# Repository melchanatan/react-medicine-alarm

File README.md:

# medicine alarm
this is a React website for setting alarm clock connected to ESP32

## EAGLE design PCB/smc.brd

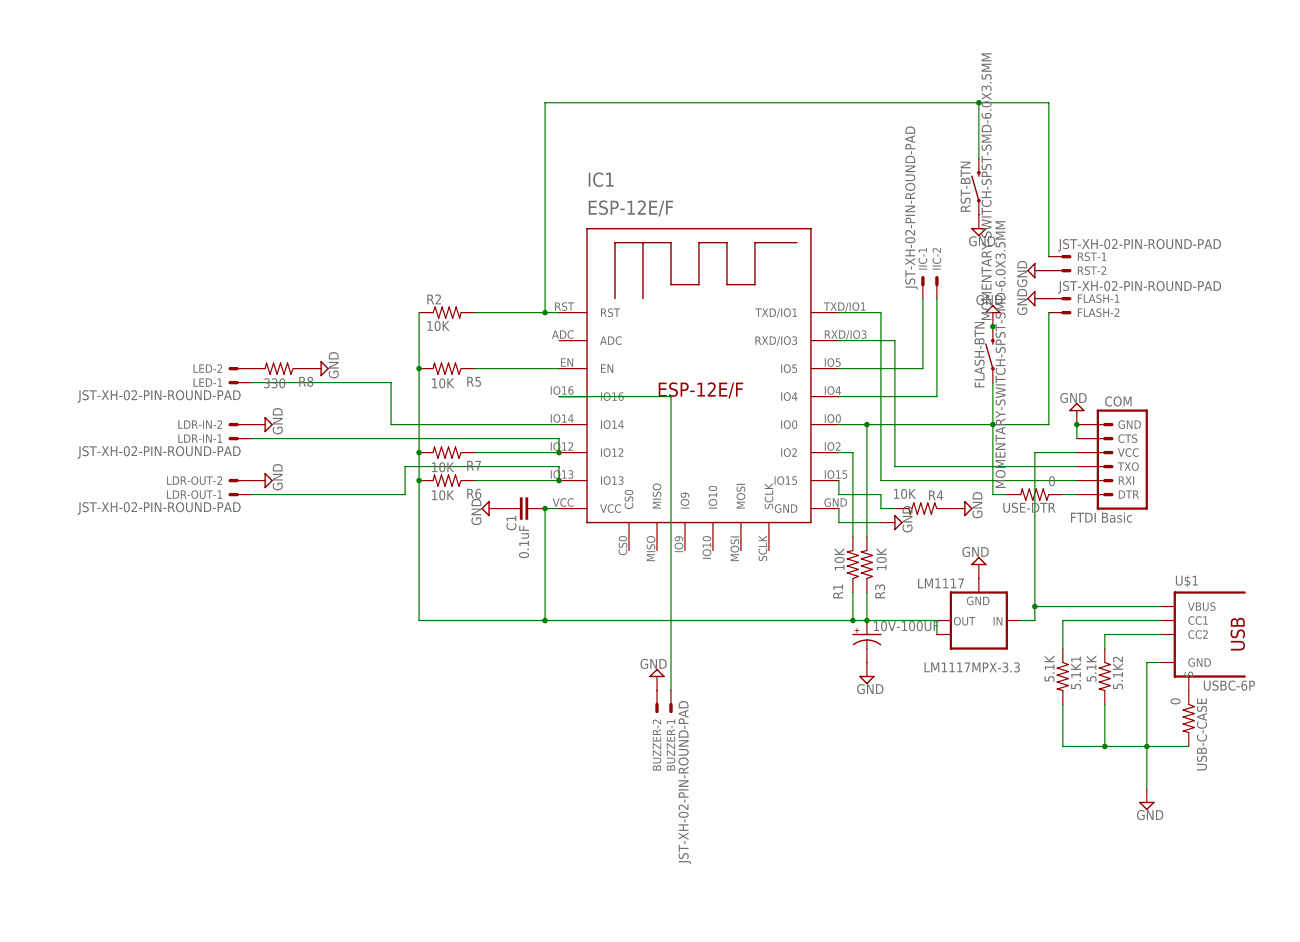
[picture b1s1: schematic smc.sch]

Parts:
5.1K1, 5.1K2: 5.1K; 0603-RES
10V-100UF: CPOL-USA/3216-18W; A/3216-18W
BUZZER: JST-XH-02-PIN-ROUND-PAD; JST-XH-02-PACKAGE-ROUND-PAD
C1: 0.1uF; 0603-CAP
COM: FTDI Basic; 1X06
FLASH: JST-XH-02-PIN-ROUND-PAD; JST-XH-02-PACKAGE-ROUND-PAD
FLASH-BTN: MOMENTARY-SWITCH-SPST-SMD-6.0X3.5MM; TACTILE_SWITCH_SMD_6.0X3.5MM
IC1: ESP-12E/F; ESP-12E
IIC: JST-XH-02-PIN-ROUND-PAD; JST-XH-02-PACKAGE-ROUND-PAD
LDR-IN: JST-XH-02-PIN-ROUND-PAD; JST-XH-02-PACKAGE-ROUND-PAD
LDR-OUT: JST-XH-02-PIN-ROUND-PAD; JST-XH-02-PACKAGE-ROUND-PAD
LED: JST-XH-02-PIN-ROUND-PAD; JST-XH-02-PACKAGE-ROUND-PAD
LM1117: LM1117MPX-3.3; SOT223
R1, R2, R3, R4, R5, R6, R7: 10K; 0603-RES
R8: 330; 0603-RES
RST: JST-XH-02-PIN-ROUND-PAD; JST-XH-02-PACKAGE-ROUND-PAD
RST-BTN: MOMENTARY-SWITCH-SPST-SMD-6.0X3.5MM; TACTILE_SWITCH_SMD_6.0X3.5MM
U$1: USBC-6P; USCX-06FX-XXMX-01
USB-C-CASE: 0; 0603-RES
USE-DTR: 0; 0603-RES

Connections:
3V3: 10V-100UF.+, C1.1, IC1.VCC, LM1117.2 (OUT), LM1117.TAB (OUT1), R1.1, R2.1, R3.1, R5.2, R6.2, R7.2
5V: COM.4 (VCC), LM1117.3 (IN), U$1.VBUS1 (VBUS), U$1.VBUS2 (VBUS)
GND: 5.1K1.2, 5.1K2.2, 10V-100UF.-, BUZZER.2, C1.2, COM.5 (CTS), COM.6 (GND), FLASH.1, FLASH-BTN.2, IC1.GND, LDR-IN.2, LDR-OUT.2, LM1117.1 (GND), R4.1, R8.1, RST.2, RST-BTN.1, U$1.GND1 (GND), U$1.GND2 (GND), USB-C-CASE.2
IO0: FLASH.2, FLASH-BTN.1, IC1.IO0, R3.2, USE-DTR.2
IO2: IC1.IO2, R1.2
unnamed: IC1.IO15, R4.2
unnamed: IC1.EN, R5.1
unnamed: IC1.IO12, LDR-IN.1, R7.1
unnamed: IC1.IO13, LDR-OUT.1, R6.1
unnamed: LED.2, R8.2
unnamed: COM.3 (TXO), IC1.RXD/IO3
unnamed: COM.2 (RXI), IC1.TXD/IO1
unnamed: COM.1 (DTR), USE-DTR.1
unnamed: U$1.SHIELD1 (S), U$1.SHIELD2 (S), U$1.SHIELD3 (S), U$1.SHIELD4 (S), USB-C-CASE.1
unnamed: IC1.IO14, LED.1
unnamed: 5.1K2.1, U$1.CC2
unnamed: 5.1K1.1, U$1.CC1
unnamed: BUZZER.1, IC1.IO16
unnamed: IC1.IO5, IIC.1
unnamed: IC1.IO4, IIC.2
RST: IC1.RST, R2.2, RST.1, RST-BTN.2

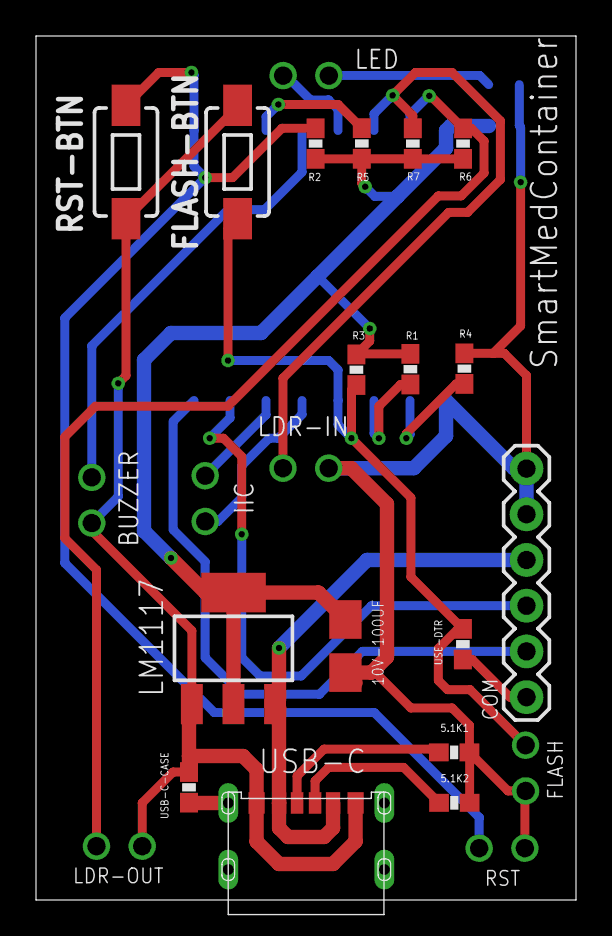
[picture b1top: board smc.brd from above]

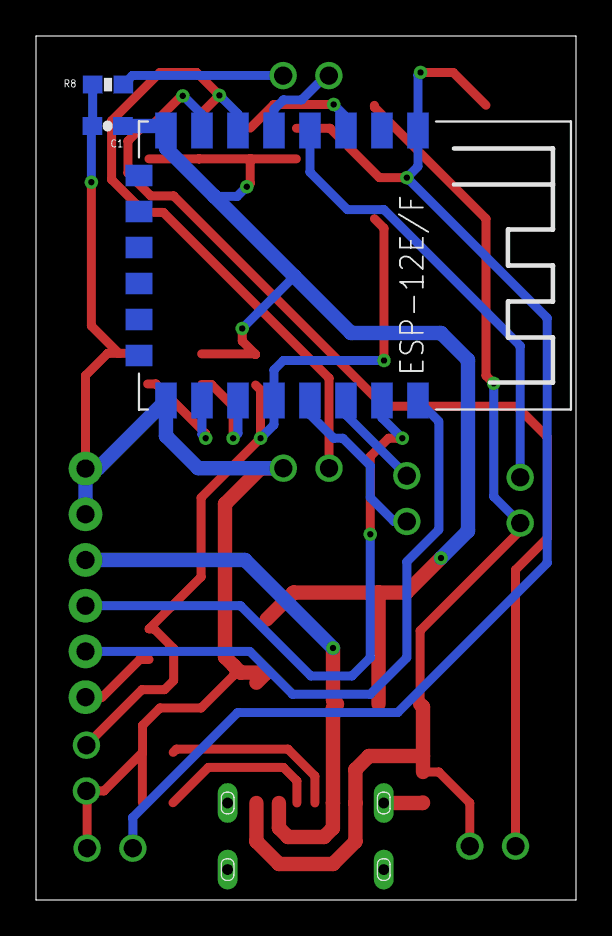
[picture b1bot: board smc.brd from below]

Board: 2 copper layers, 30.0 x 48.0 mm, 27 parts (3 on the bottom side), 21 nets.

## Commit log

2021-11-26 test
2021-11-27 connect firebase
2021-11-27 fix styles
2021-12-07 add pcb

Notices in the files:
parts and their libraries:
SparkFun-Switches: Licensing: Creative Commons ShareAlike 4.0 International - https://creativecommons.org/licenses/by-sa/4.0
